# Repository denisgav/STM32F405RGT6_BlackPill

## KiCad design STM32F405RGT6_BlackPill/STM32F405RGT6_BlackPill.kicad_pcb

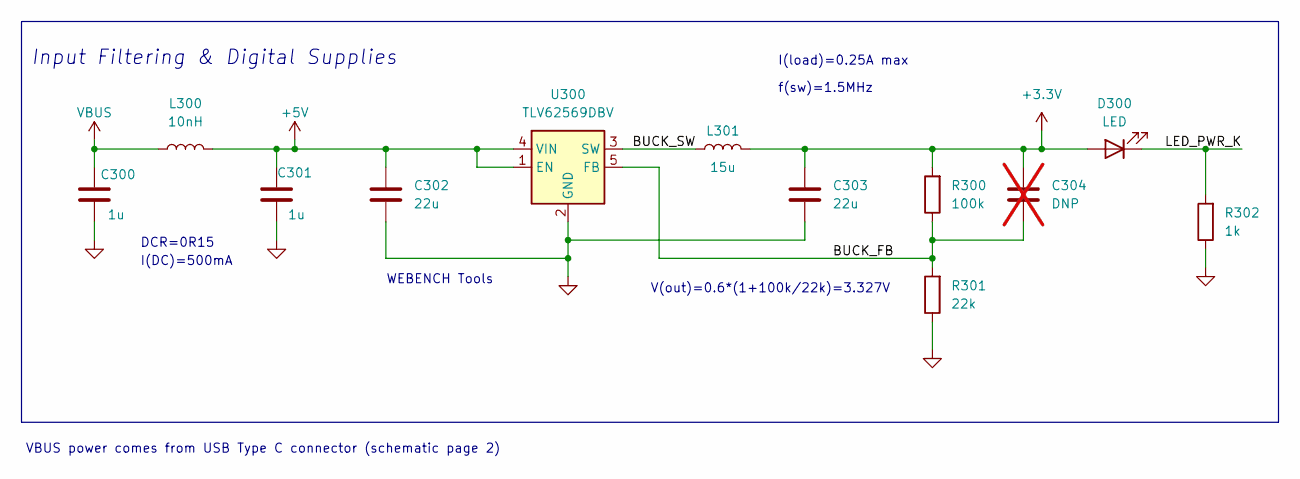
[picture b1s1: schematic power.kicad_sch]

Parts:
C300, C301: 1u; C_0603_1608Metric; DigiKey Part Number 1276-1946-6-ND
C302, C303: 22u; C_0805_2012Metric; DigiKey Part Number 1276-6687-6-ND
C304: DNP; C_0402_1005Metric; not fitted
D300: LED; LED_0603_1608Metric; DigiKey Part Number 732-4971-6-ND
L300: 10nH; L_0402_1005Metric; DigiKey Part Number 712-LRC0402CJ10NGV001TDKR-ND
L301: 15u; MWSA0603S; DigiKey Part Number 3442-MWSA0603S-150MTDKR-ND
R300: 100k; R_0402_1005Metric; DigiKey Part Number P100KLDKR-ND
R301: 22k; R_0402_1005Metric; DigiKey Part Number P22.0KLDKR-ND
R302: 1k; R_0402_1005Metric; DigiKey Part Number P1.00KLDKR-ND
U300: TLV62569DBV; SOT-23-5; DigiKey Part Number 296-47360-6-ND

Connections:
+3.3V: C303.1, C304.1, D300.2 (A), L301.2, R300.2; also elsewhere on the board
+5V: C301.1, C302.1, L300.2, U300.1 (EN), U300.4 (VIN); also elsewhere on the board
/power/BUCK_FB: C304.2, R300.1, R301.2, U300.5 (FB)
/power/BUCK_SW: L301.1, U300.3 (SW)
/power/LED_PWR_K: D300.1 (K), R302.2
GND: C300.2, C301.2, C302.2, C303.2, R301.1, R302.1, U300.2 (GND); also elsewhere on the board
VBUS: C300.1, L300.1; also elsewhere on the board

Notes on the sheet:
f(sw)=1.5MHz
V(out)=0.6*(1+100k/22k)=3.327V
VBUS power comes from USB Type C connector (schematic page 2)
I(load)=0.25A max
DCR=0R15
WEBENCH Tools
Input Filtering & Digital Supplies
I(DC)=500mA

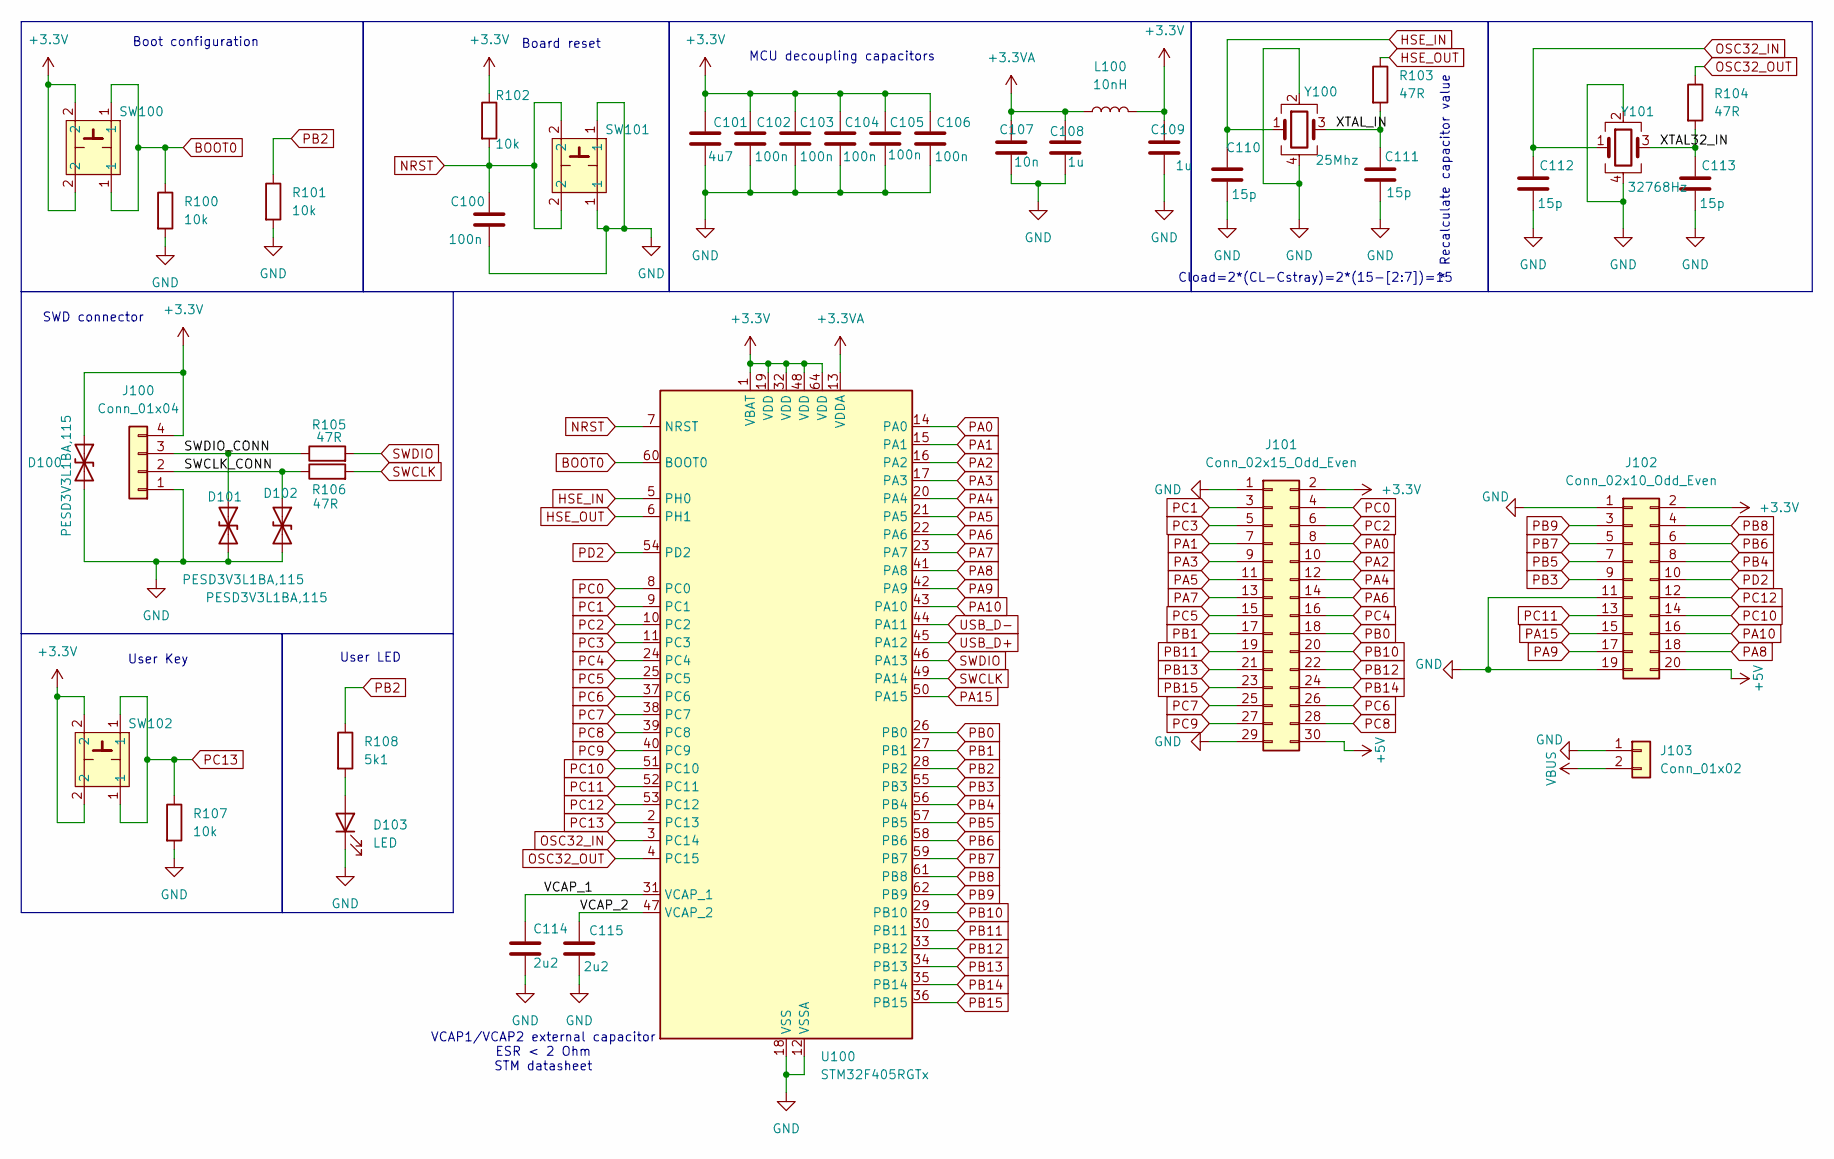
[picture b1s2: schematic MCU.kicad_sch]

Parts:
C100, C102, C103, C104, C105, C106: 100n; C_0402_1005Metric; DigiKey Part Number 1276-1002-6-ND
C101: 4u7; C_0603_1608Metric; DigiKey Part Number 1276-1044-6-ND
C107: 10n; C_0402_1005Metric; DigiKey Part Number 1276-1028-6-ND
C108, C109: 1u; C_0603_1608Metric; DigiKey Part Number 1276-1946-6-ND
C110, C111, C112, C113: 15p; C_0402_1005Metric; DigiKey Part Number 490-11191-6-ND
C114, C115: 2u2; C_0805_2012Metric; DigiKey Part Number 445-1420-6-ND
D100, D101, D102: PESD3V3L1BA,115; D_SOD-323; DigiKey Part Number 1727-3825-6-ND
D103: LED; LED_0603_1608Metric; DigiKey Part Number 732-4971-6-ND
J100: Conn_01x04; PinHeader_1x04_P2.54mm_Vertical
J101: Conn_02x15_Odd_Even; PinHeader_2x15_P2.54mm_Vertical
J102: Conn_02x10_Odd_Even; PinHeader_2x10_P2.54mm_Vertical
J103: Conn_01x02; PinHeader_1x02_P2.54mm_Vertical
L100: 10nH; L_0402_1005Metric; DigiKey Part Number 712-LRC0402CJ10NGV001TDKR-ND
R100, R101, R102, R107: 10k; R_0402_1005Metric; DigiKey Part Number 1276-3431-6-ND
R103, R104, R105, R106: 47R; R_0402_1005Metric; DigiKey Part Number P47JDKR-ND
R108: 5k1; R_0402_1005Metric; DigiKey Part Number P5.1KDCDKR-ND
SW100, SW101, SW102: SW_PUSH_6mm
U100: STM32F405RGTx; LQFP-64_10x10mm_P0.5mm; DigiKey Part Number 497-11767-ND
Y100: 25Mhz; Crystal_SMD_3225-4Pin_3.2x2.5mm; DigiKey Part Number 535-ASE-25.000MHZ-L-C-TDKR-ND
Y101: 32768Hz; Crystal_SMD_3225-4Pin_3.2x2.5mm; DigiKey Part Number 535-ASEK-32.768KHZ-L-R-TDKR-ND

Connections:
+3.3V: C101.1, C102.1, C103.1, C104.1, C105.1, C106.1, C109.1, D100.1 (A1), J100.4, J101.2, J102.2, L100.2, R102.1, SW100.2, SW102.2, U100.1 (VBAT), U100.19 (VDD), U100.32 (VDD), U100.48 (VDD), U100.64 (VDD); also elsewhere on the board
+3.3VA: C107.1, C108.1, L100.1, U100.13 (VDDA)
+5V: J101.30, J102.20; also elsewhere on the board
/MCU/SWCLK_CONN: D102.1 (A1), J100.2, R106.1
/MCU/SWDIO_CONN: D101.1 (A1), J100.3, R105.1
/MCU/VCAP_1: C114.1, U100.31 (VCAP_1)
/MCU/VCAP_2: C115.1, U100.47 (VCAP_2)
/MCU/XTAL32_IN: C113.1, R104.2, Y101.3
/MCU/XTAL_IN: C111.1, R103.2, Y100.3
BOOT0: R100.1, SW100.1, U100.60 (BOOT0)
GND: C100.2, C101.2, C102.2, C103.2, C104.2, C105.2, C106.2, C107.2, C108.2, C109.2, C110.2, C111.2, C112.2, C113.2, C114.2, C115.2, D100.2 (A2), D101.2 (A2), D102.2 (A2), D103.1 (K), J100.1, J101.1, J101.29, J102.1, J102.11, J102.19, J103.1, R100.2, R101.2, R107.2, SW101.1, U100.12 (VSSA), U100.18 (VSS), U100.63 (VSS), Y100.2, Y100.4, Y101.2, Y101.4; also elsewhere on the board
HSE_IN: C110.1, U100.5 (PH0), Y100.1
HSE_OUT: R103.1, U100.6 (PH1)
NRST: C100.1, R102.2, SW101.2, U100.7 (NRST)
unnamed: D103.2 (A), R108.2
OSC32_IN: C112.1, U100.3 (PC14), Y101.1
OSC32_OUT: R104.1, U100.4 (PC15)
PA0: J101.8, U100.14 (PA0)
PA1: J101.7, U100.15 (PA1)
PA2: J101.10, U100.16 (PA2)
PA3: J101.9, U100.17 (PA3)
PA4: J101.12, U100.20 (PA4)
PA5: J101.11, U100.21 (PA5)
PA6: J101.14, U100.22 (PA6)
PA7: J101.13, U100.23 (PA7)
PA8: J102.18, U100.41 (PA8)
PA9: J102.17, U100.42 (PA9)
PA10: J102.16, U100.43 (PA10)
PA15: J102.15, U100.50 (PA15)
PB0: J101.18, U100.26 (PB0)
PB1: J101.17, U100.27 (PB1)
PB2: R101.1, R108.1, U100.28 (PB2)
PB3: J102.9, U100.55 (PB3)
PB4: J102.8, U100.56 (PB4)
PB5: J102.7, U100.57 (PB5)
PB6: J102.6, U100.58 (PB6)
PB7: J102.5, U100.59 (PB7)
PB8: J102.4, U100.61 (PB8)
PB9: J102.3, U100.62 (PB9)
PB10: J101.20, U100.29 (PB10)
PB11: J101.19, U100.30 (PB11)
PB12: J101.22, U100.33 (PB12)
PB13: J101.21, U100.34 (PB13)
PB14: J101.24, U100.35 (PB14)
PB15: J101.23, U100.36 (PB15)
PC0: J101.4, U100.8 (PC0)
PC1: J101.3, U100.9 (PC1)
PC2: J101.6, U100.10 (PC2)
PC3: J101.5, U100.11 (PC3)
PC4: J101.16, U100.24 (PC4)
PC5: J101.15, U100.25 (PC5)
PC6: J101.26, U100.37 (PC6)
PC7: J101.25, U100.38 (PC7)
PC8: J101.28, U100.39 (PC8)
PC9: J101.27, U100.40 (PC9)
PC10: J102.14, U100.51 (PC10)
PC11: J102.13, U100.52 (PC11)
PC12: J102.12, U100.53 (PC12)
PC13: R107.1, SW102.1, U100.2 (PC13)
PD2: J102.10, U100.54 (PD2)
SWCLK: R106.2, U100.49 (PA14)
SWDIO: R105.2, U100.46 (PA13)
USB_D+: U100.45 (PA12); also elsewhere on the board
USB_D-: U100.44 (PA11); also elsewhere on the board
VBUS: J103.2; also elsewhere on the board

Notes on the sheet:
Cload=2*(CL-Cstray)=2*(15-[2:7])=15
MCU decoupling capacitors
VCAP1/VCAP2 external capacitor ESR < 2 Ohm STM datasheet
Board reset
User Key
SWD connector
User LED
* Recalculate capacitor value
Boot configuration

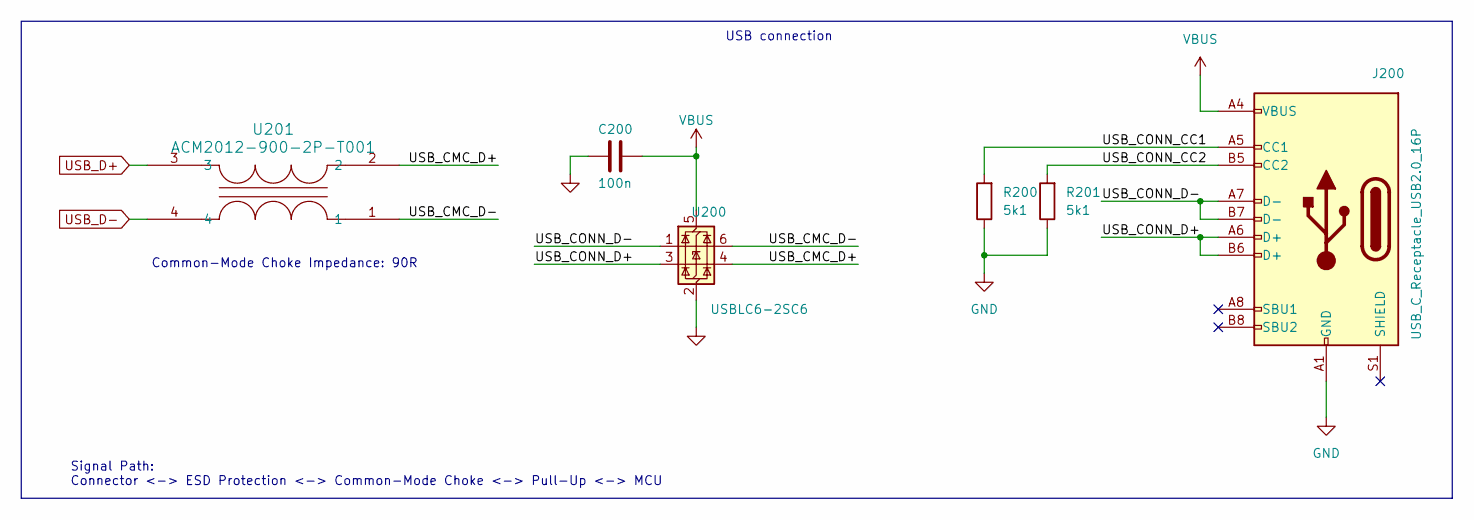
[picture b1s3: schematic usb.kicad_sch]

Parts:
C200: 100n; C_0402_1005Metric; DigiKey Part Number 1276-1002-6-ND
J200: USB_C_Receptacle_USB2.0_16P; USB_C_Receptacle_HCTL_HC-TYPE-C-16P-01A; DigiKey Part Number 664-12402012E212ADKR-ND
R200, R201: 5k1; R_0402_1005Metric; DigiKey Part Number P5.1KDCDKR-ND
U200: USBLC6-2SC6; SOT-23-6; DigiKey Part Number 497-5235-6-ND
U201: ACM2012-900-2P-T001; SMT_0-2P-T001_TDK; DigiKey Part Number 445-15969-6-ND

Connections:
/USB/USB_CMC_D+: U200.4 (I/O2), U201.2
/USB/USB_CMC_D-: U200.6 (I/O1), U201.1
/USB/USB_CONN_CC1: J200.A5 (CC1), R200.2
/USB/USB_CONN_CC2: J200.B5 (CC2), R201.2
/USB/USB_CONN_D+: J200.A6 (D+), J200.B6 (D+), U200.3 (I/O2)
/USB/USB_CONN_D-: J200.A7 (D-), J200.B7 (D-), U200.1 (I/O1)
GND: C200.2, J200.A1 (GND), J200.A12 (GND), J200.B1 (GND), J200.B12 (GND), R200.1, R201.1, U200.2 (GND); also elsewhere on the board
USB_D+: U201.3; also elsewhere on the board
USB_D-: U201.4; also elsewhere on the board
VBUS: C200.1, J200.A4 (VBUS), J200.A9 (VBUS), J200.B4 (VBUS), J200.B9 (VBUS), U200.5 (VBUS); also elsewhere on the board

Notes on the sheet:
Signal Path: Connector <-> ESD Protection <-> Common-Mode Choke <-> Pull-Up <-> MCU
USB connection
Common-Mode Choke Impedance: 90R

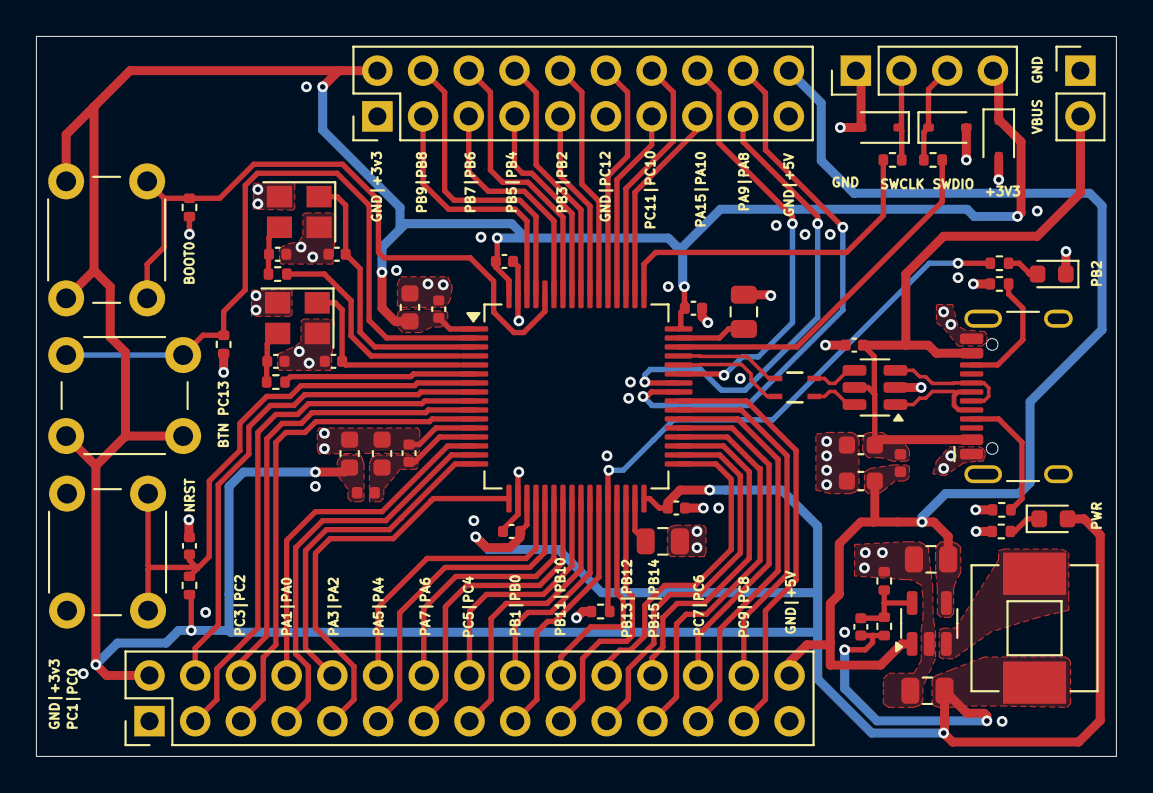
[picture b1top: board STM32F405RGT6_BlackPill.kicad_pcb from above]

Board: 4 copper layers, 60.0 x 40.0 mm, 58 parts (0 on the bottom side), 74 nets.

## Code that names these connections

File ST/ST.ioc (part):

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Mcu.Name=STM32F405RGTx
Mcu.Package=LQFP64
Mcu.UserName=STM32F405RGTx
PA11.Mode=Device_Only
PA11.Signal=USB_OTG_FS_DM
PA12.Mode=Device_Only
PA12.Signal=USB_OTG_FS_DP
PA13.Mode=Serial_Wire
PA13.Signal=SYS_JTMS-SWDIO
PA14.Mode=Serial_Wire
PA14.Signal=SYS_JTCK-SWCLK
PC14-OSC32_IN.Mode=LSE-External-Oscillator
PC14-OSC32_IN.Signal=RCC_OSC32_IN
PC15-OSC32_OUT.Mode=LSE-External-Oscillator
PC15-OSC32_OUT.Signal=RCC_OSC32_OUT
PH0-OSC_IN.Mode=HSE-External-Oscillator
PH0-OSC_IN.Signal=RCC_OSC_IN
PH1-OSC_OUT.Mode=HSE-External-Oscillator
PH1-OSC_OUT.Signal=RCC_OSC_OUT
RCC.HSE_VALUE=25000000
RCC.SYSCLKFreq_VALUE=168000000
RCC.SYSCLKSource=RCC_SYSCLKSOURCE_PLLCLK
board=custom

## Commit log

2024-12-23 Add power and USB scheme
2024-12-23 First version of the scheme
2024-12-23 Essential part of the BOM fill
2024-12-23 BOM table fill
2024-12-23 Initial components placement
2024-12-24 Border outline
2024-12-24 Signal routing (bottom part)
2024-12-24 Signal routing (upper part)
2024-12-24 Minor DCR fixes
2024-12-24 All signals routed
2024-12-25 VBUS | GND connector, manufacture files
2024-12-25 Add BOM file
2024-12-26 Production files JLCPCB
